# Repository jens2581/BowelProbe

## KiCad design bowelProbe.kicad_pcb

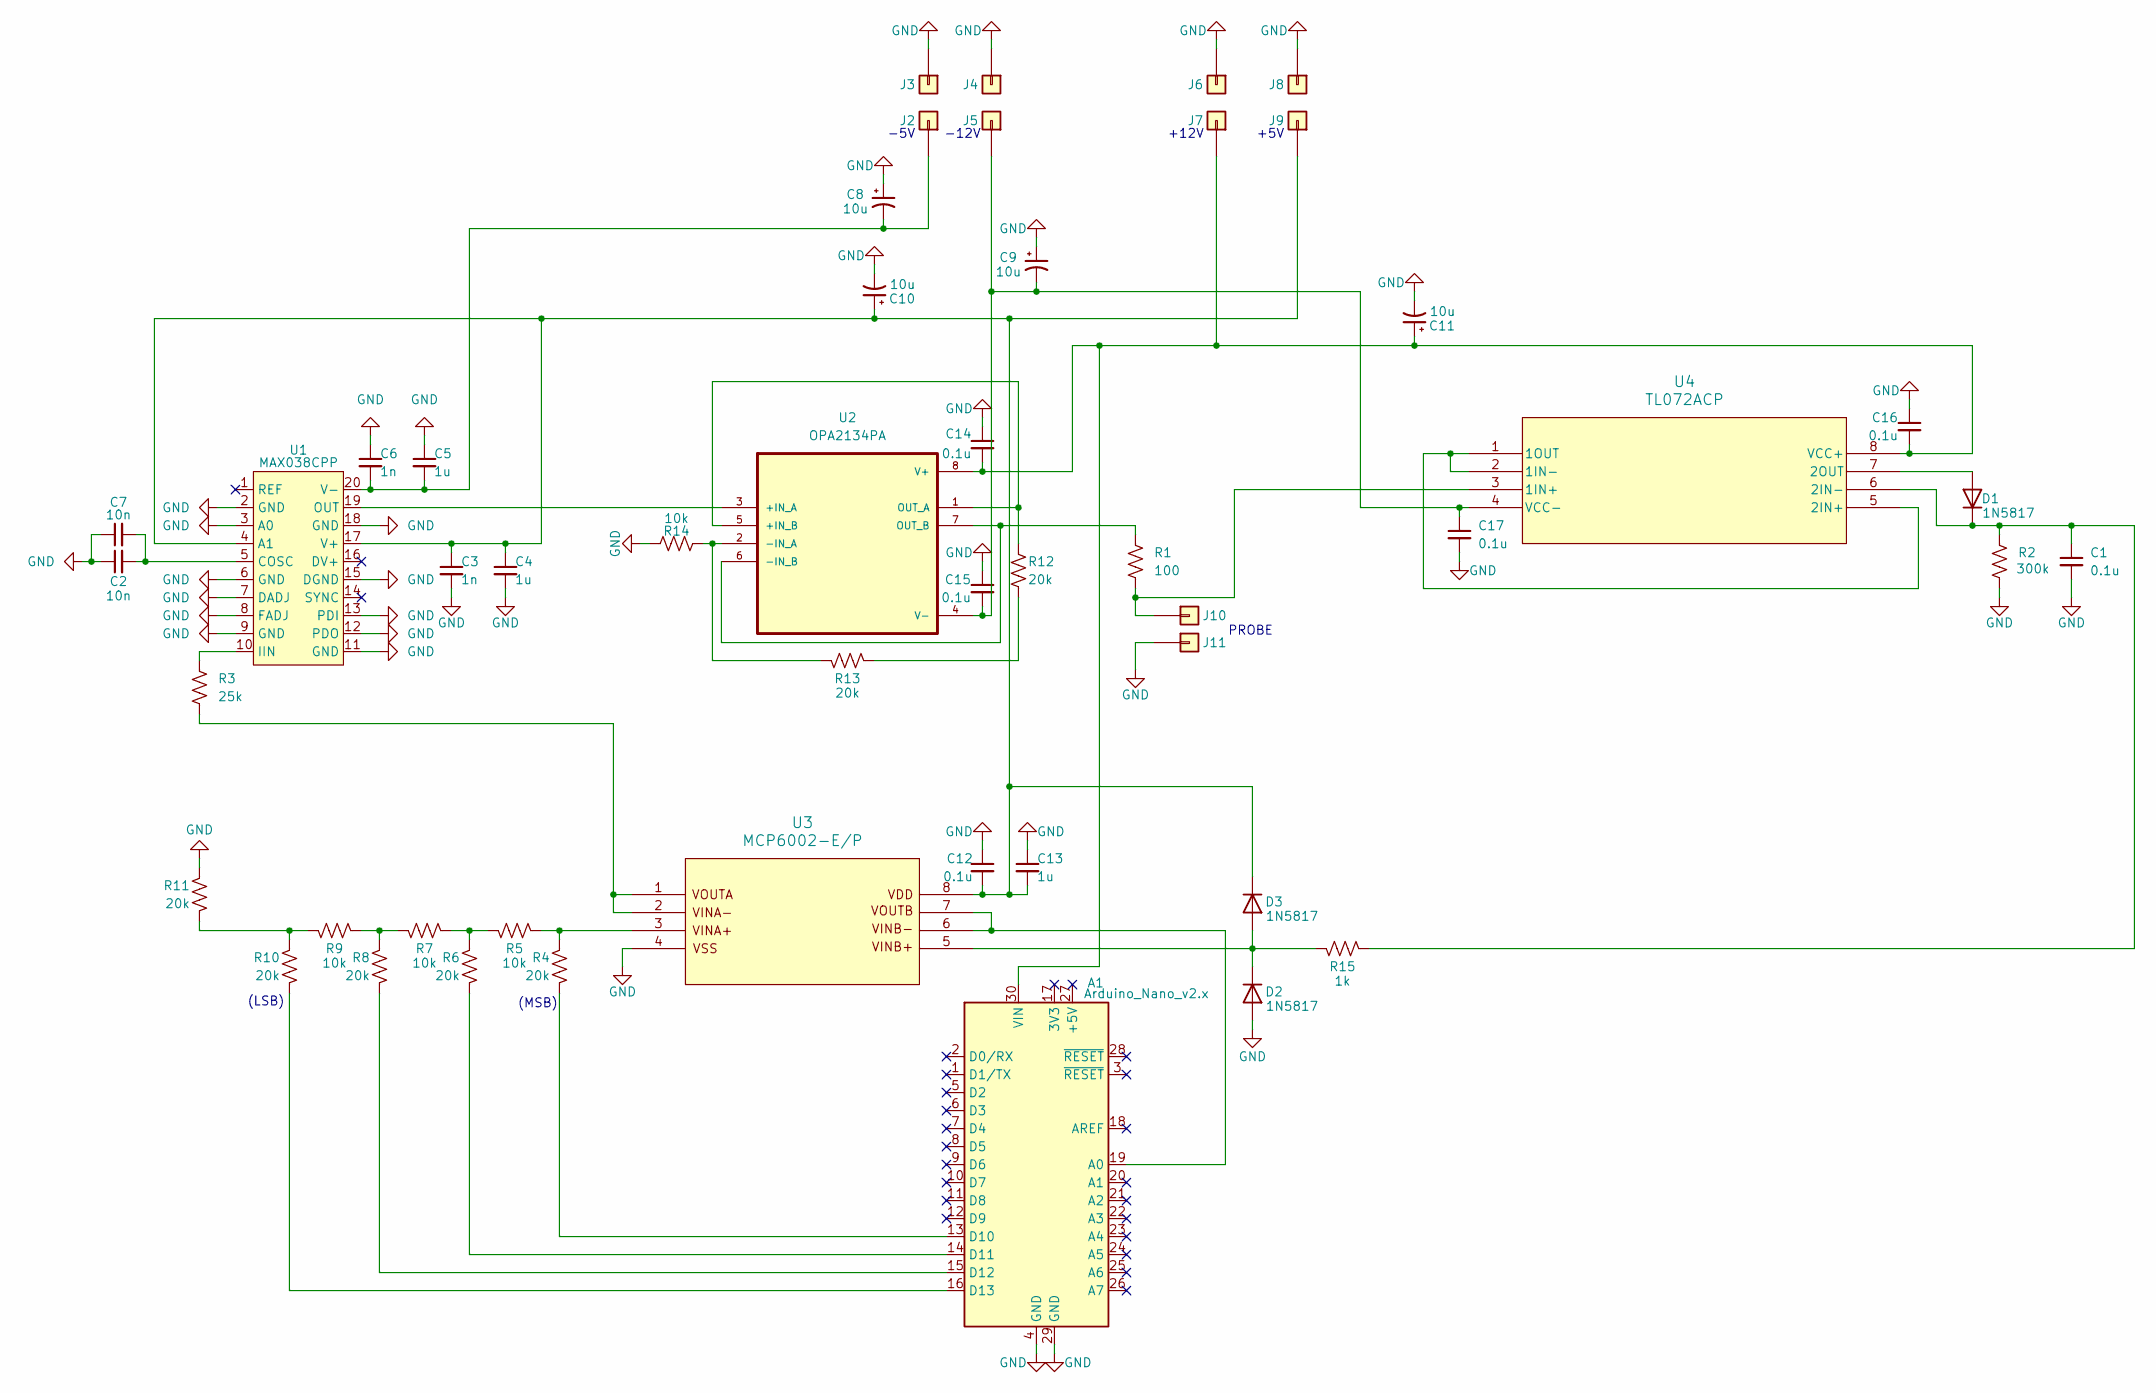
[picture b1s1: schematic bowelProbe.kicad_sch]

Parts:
A1: Arduino_Nano_v2.x; Arduino_Nano
C1, C12, C14, C15, C16, C17: 0.1u; Capacitor-10n
C2, C7: 10n; Capacitor-10n
C3, C6: 1n; Capacitor-10n
C4, C5, C13: 1u; Capacitor-10n
C8, C9, C10, C11: 10u; Capacitor-10u
D1, D2, D3: 1N5817
J2, J5, J7, J9: Conn_01x01; CT3149-2
J3, J4, J6, J8: Conn_01x01; CT3149-0
J10, J11: Conn_01x01; CT3149-5
R1: 100; Resistor-20k
R2: 300k; Resistor-20k
R3: 25k; Resistor-20k
R4, R6, R8, R10, R11, R12, R13: 20k; Resistor-20k
R5, R7, R9, R14: 10k; Resistor-20k
R15: 1k; Resistor-20k
U1: MAX038CPP
U2: OPA2134PA; DIP794W45P254L959H508Q8
U3: MCP6002-E/P; PDIP8_300MC_MCH
U4: TL072ACP; P8

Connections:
GND: A1.4 (GND), A1.29 (GND), C1.2, C2.1, C3.2, C4.2, C5.1, C6.1, C7.1, C8.1, C9.1, C10.2, C11.2, C12.1, C13.1, C14.1, C15.1, C16.1, C17.2, D2.2 (A), J3.1, J4.1, J6.1, J8.1, J11.1, R2.2, R11.1, R14.1, U1.2 (GND), U1.3 (A0), U1.6 (GND), U1.7 (DADJ), U1.8 (FADJ), U1.9 (GND), U1.11 (GND), U1.12 (PDO), U1.13 (PDI), U1.15 (DGND), U1.18 (GND), U3.4
unnamed: A1.19 (A0), U3.6, U3.7
unnamed: A1.13 (D10), R4.2
unnamed: A1.14 (D11), R6.2
unnamed: A1.15 (D12), R8.2
unnamed: A1.16 (D13), R10.2
unnamed: A1.30 (VIN), C11.1, C14.2, C16.2, J7.1, U2.8 (V+), U4.8 (VCC+)
unnamed: D1.2 (A), U4.7 (2OUT)
unnamed: C1.1, D1.1 (K), R2.1, R15.1, U4.6 (2IN-)
unnamed: D2.1 (K), D3.2 (A), R15.2, U3.5
unnamed: C3.1, C4.1, C10.1, C12.2, C13.2, D3.1 (K), J9.1, U1.4 (A1), U1.17 (V+), U3.8
unnamed: C5.2, C6.2, C8.2, J2.1, U1.20 (V-)
unnamed: C9.2, C15.2, C17.1, J5.1, U2.4 (V-), U4.4 (VCC-)
unnamed: J10.1, R1.2, U4.3 (1IN+)
unnamed: R3.2, U3.1, U3.2
unnamed: R4.1, R5.1, U3.3
unnamed: R5.2, R6.1, R7.1
unnamed: R7.2, R8.1, R9.1
unnamed: R9.2, R10.1, R11.2
unnamed: R12.2, R13.1
unnamed: C2.2, C7.2, U1.5 (COSC)
unnamed: R3.1, U1.10 (IIN)
unnamed: U1.19 (OUT), U2.3 (+IN_A)
unnamed: R12.1, U2.1 (OUT_A), U2.5 (+IN_B)
unnamed: R13.2, R14.2, U2.2 (-IN_A)
unnamed: R1.1, U2.6 (-IN_B), U2.7 (OUT_B)
unnamed: U4.1 (1OUT), U4.2 (1IN-), U4.5 (2IN+)

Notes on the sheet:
(LSB)
+5V
+12V
-5V
PROBE
-12V
(MSB)

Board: 2 copper layers, 50 parts (0 on the bottom side), 27 nets, no tracks yet.

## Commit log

2026-01-13 Finished Schematic
    Schematic was updated and completed. Awaiting final checks to ensure proper wiring.
    Next steps: choose components, assign footprints accordingly, begin PCB placement and routing.
2026-01-17 Schematic Nearly Finished
    Added important decoupling capacitors. Added in all necessary symbols, footprints, 3D files (except for probe and voltages).
    To do:
    - Determine plan for probe and power pins
    - Set up their symbols, footprints, 3D files
    - Final schematic review
    - Move on to PCB layout and routing
2026-01-18 Schematic and PCB update
    Finished schematic. Finished general PCB layout.
    To do:
    - Finely touch up PCB layout
    - Review layout
    - Begin routing
2026-01-20 PCB Passed Final Check
    Updated PCB reference designators (both in schematic and layout). Gave final check to ensure proper PCB layout and routing.
